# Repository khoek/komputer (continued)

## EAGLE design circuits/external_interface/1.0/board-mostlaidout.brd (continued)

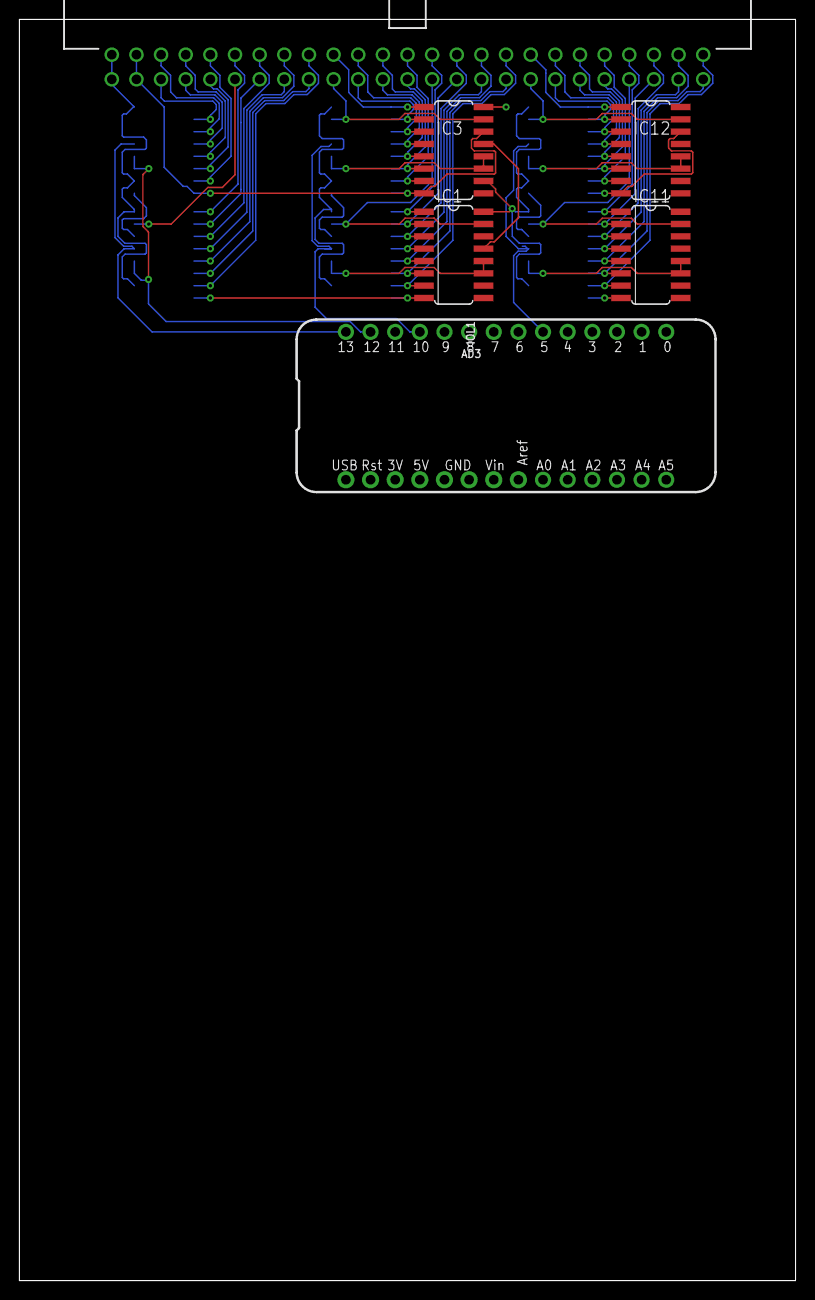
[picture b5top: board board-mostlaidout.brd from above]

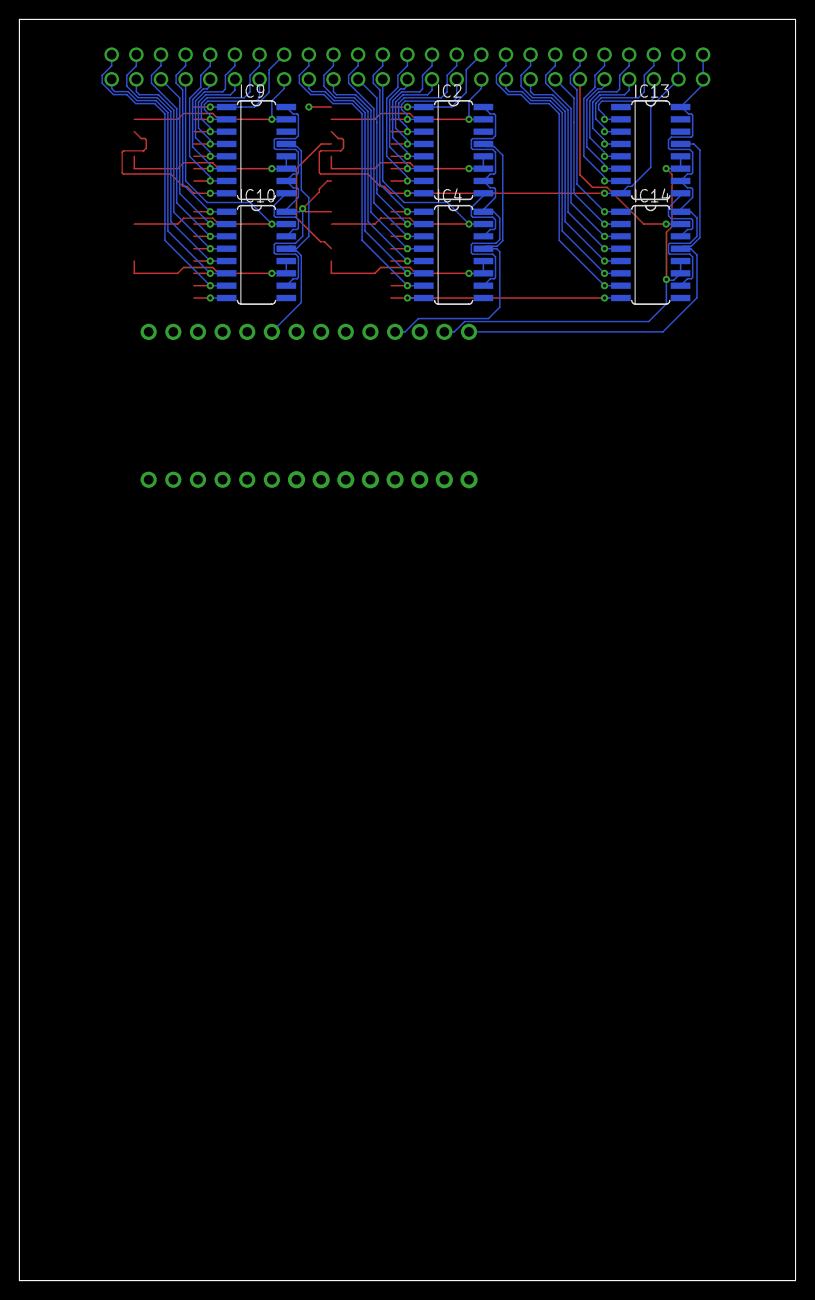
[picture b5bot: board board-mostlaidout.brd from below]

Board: 2 copper layers, 80.0 x 130.0 mm, 15 parts (6 on the bottom side), 66 nets.

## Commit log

2019-11-12 EEPROM programmer (eeagle) server and client
2019-11-12 Add README
2019-11-17 Some circuit designs
2019-12-12 Add module testers
2019-12-16 Add ALU flags register test
2019-12-17 Fully enable ALU tests
2019-12-23 Add schematics
2019-12-23 Relocate board tests
2019-12-23 Improve README.md
